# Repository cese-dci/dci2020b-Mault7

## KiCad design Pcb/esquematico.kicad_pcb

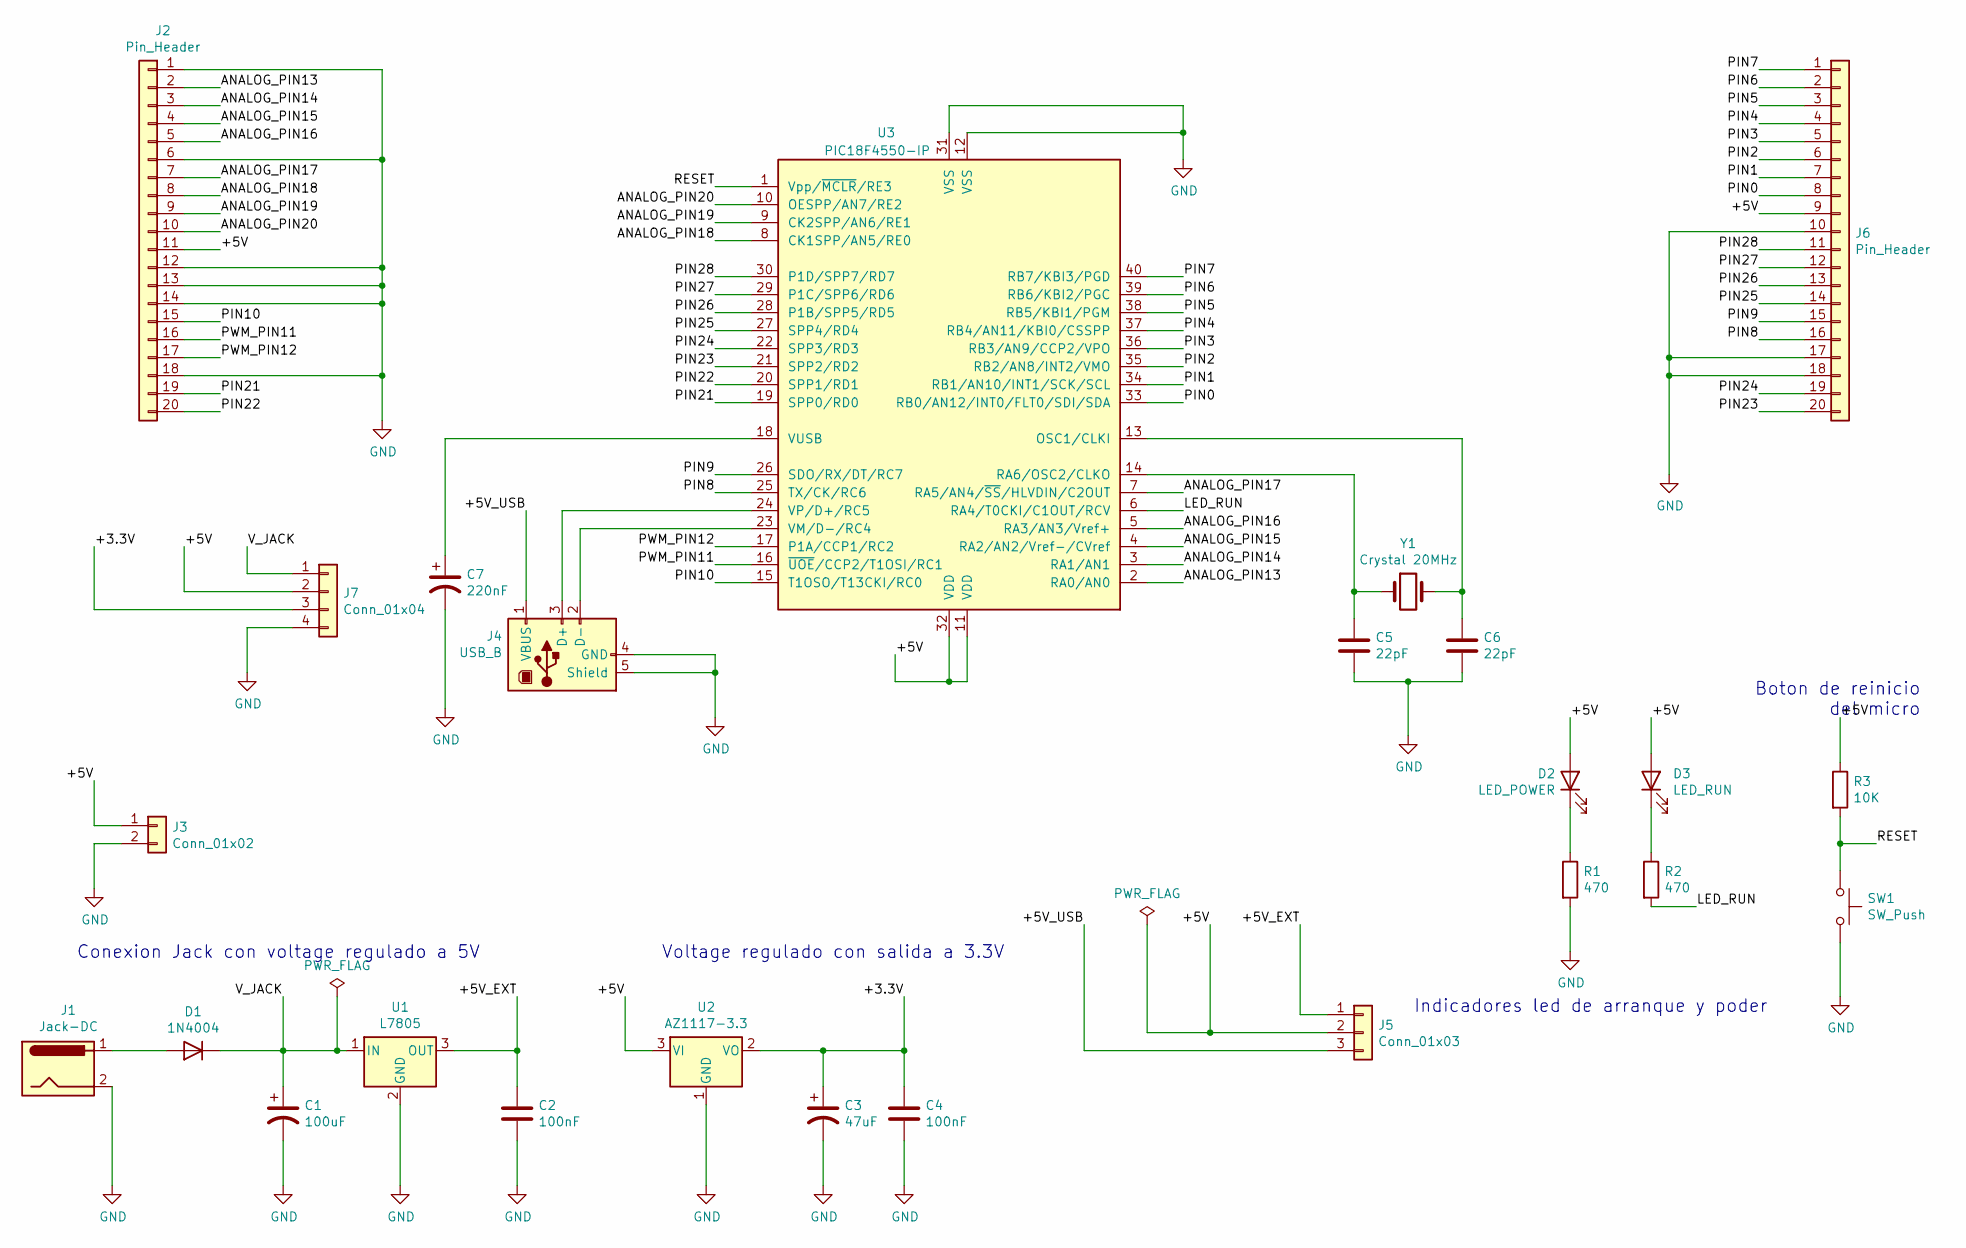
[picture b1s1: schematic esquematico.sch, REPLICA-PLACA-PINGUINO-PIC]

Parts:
C1: 100uF; CP_Radial_D5.0mm_P2.50mm
C2, C4: 100nF; C_Disc_D5.0mm_W2.5mm_P2.50mm
C3: 47uF; CP_Radial_D5.0mm_P2.50mm
C5, C6: 22pF; C_Disc_D3.8mm_W2.6mm_P2.50mm
C7: 220nF; CP_Radial_Tantal_D5.0mm_P5.00mm
D1: 1N4004; D_DO-41_SOD81_P7.62mm_Horizontal
D2: LED_POWER; LED_D3.0mm
D3: LED_RUN; LED_D3.0mm
J1: Jack-DC; BarrelJack_Horizontal
J2, J6: Pin_Header; PinSocket_1x20_P2.54mm_Vertical
J3: Conn_01x02; PinSocket_1x02_P2.54mm_Vertical
J4: USB_B; USB_B_Lumberg_2411_02_Horizontal
J5: Conn_01x03; PinHeader_1x03_P2.54mm_Vertical
J7: Conn_01x04; PinSocket_1x04_P2.54mm_Vertical
R1, R2: 470; R_Axial_DIN0207_L6.3mm_D2.5mm_P7.62mm_Horizontal
R3: 10K; R_Axial_DIN0207_L6.3mm_D2.5mm_P7.62mm_Horizontal
SW1: SW_Push; SW_PUSH_6mm_H7.3mm
U1: L7805; TO-3P-3_Vertical
U2: AZ1117-3.3; TO-3P-3_Vertical
U3: PIC18F4550-IP; DIP-40_W15.24mm
Y1: Crystal 20MHz; Crystal_HC18-U_Vertical

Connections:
/+3.3V: C3.1, C4.1, J7.3, U2.2 (VO)
/+5V: D2.2 (A), D3.2 (A), J2.11, J3.1, J5.2, J6.9, J7.2, R3.1, U2.3 (VI), U3.11 (VDD), U3.32 (VDD)
/+5V_EXT: C2.1, J5.1, U1.3 (OUT)
/+5V_USB: J4.1 (VBUS), J5.3
/ANALOG_PIN13: J2.2, U3.2 (RA0/AN0)
/ANALOG_PIN14: J2.3, U3.3 (RA1/AN1)
/ANALOG_PIN15: J2.4, U3.4 (RA2/AN2/Vref-/CVref)
/ANALOG_PIN16: J2.5, U3.5 (RA3/AN3/Vref+)
/ANALOG_PIN17: J2.7, U3.7 (RA5/AN4/~SS~/HLVDIN/C2OUT)
/ANALOG_PIN18: J2.8, U3.8 (CK1SPP/AN5/RE0)
/ANALOG_PIN19: J2.9, U3.9 (CK2SPP/AN6/RE1)
/ANALOG_PIN20: J2.10, U3.10 (OESPP/AN7/RE2)
/LED_RUN: R2.2, U3.6 (RA4/T0CKI/C1OUT/RCV)
/PIN0: J6.8, U3.33 (RB0/AN12/INT0/FLT0/SDI/SDA)
/PIN1: J6.7, U3.34 (RB1/AN10/INT1/SCK/SCL)
/PIN2: J6.6, U3.35 (RB2/AN8/INT2/VMO)
/PIN3: J6.5, U3.36 (RB3/AN9/CCP2/VPO)
/PIN4: J6.4, U3.37 (RB4/AN11/KBI0/CSSPP)
/PIN5: J6.3, U3.38 (RB5/KBI1/PGM)
/PIN6: J6.2, U3.39 (RB6/KBI2/PGC)
/PIN7: J6.1, U3.40 (RB7/KBI3/PGD)
/PIN8: J6.16, U3.25 (TX/CK/RC6)
/PIN9: J6.15, U3.26 (SDO/RX/DT/RC7)
/PIN10: J2.15, U3.15 (T1OSO/T13CKI/RC0)
/PIN21: J2.19, U3.19 (SPP0/RD0)
/PIN22: J2.20, U3.20 (SPP1/RD1)
/PIN23: J6.20, U3.21 (SPP2/RD2)
/PIN24: J6.19, U3.22 (SPP3/RD3)
/PIN25: J6.14, U3.27 (SPP4/RD4)
/PIN26: J6.13, U3.28 (P1B/SPP5/RD5)
/PIN27: J6.12, U3.29 (P1C/SPP6/RD6)
/PIN28: J6.11, U3.30 (P1D/SPP7/RD7)
/PWM_PIN11: J2.16, U3.16 (~UOE~/CCP2/T1OSI/RC1)
/PWM_PIN12: J2.17, U3.17 (P1A/CCP1/RC2)
/RESET: R3.2, SW1.1, U3.1 (Vpp/~MCLR~/RE3)
/V_JACK: C1.1, D1.1 (K), J7.1, U1.1 (IN)
GND: C1.2, C2.2, C3.2, C4.2, C5.2, C6.2, C7.2, J1.2, J2.1, J2.6, J2.12, J2.13, J2.14, J2.18, J3.2, J4.4 (GND), J4.5 (Shield), J6.10, J6.17, J6.18, J7.4, R1.2, SW1.2, U1.2 (GND), U2.1 (GND), U3.12 (VSS), U3.31 (VSS)
unnamed: C5.1, U3.14 (RA6/OSC2/CLKO), Y1.1
unnamed: C6.1, U3.13 (OSC1/CLKI), Y1.2
unnamed: C7.1, U3.18 (VUSB)
unnamed: D1.2 (A), J1.1
unnamed: D2.1 (K), R1.1
unnamed: D3.1 (K), R2.1
unnamed: J4.2 (D-), U3.23 (VM/D-/RC4)
unnamed: J4.3 (D+), U3.24 (VP/D+/RC5)

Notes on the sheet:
Conexion Jack con voltage regulado a 5V
Voltage regulado con salida a 3.3V
Boton de reinicio del micro
Indicadores led de arranque y poder

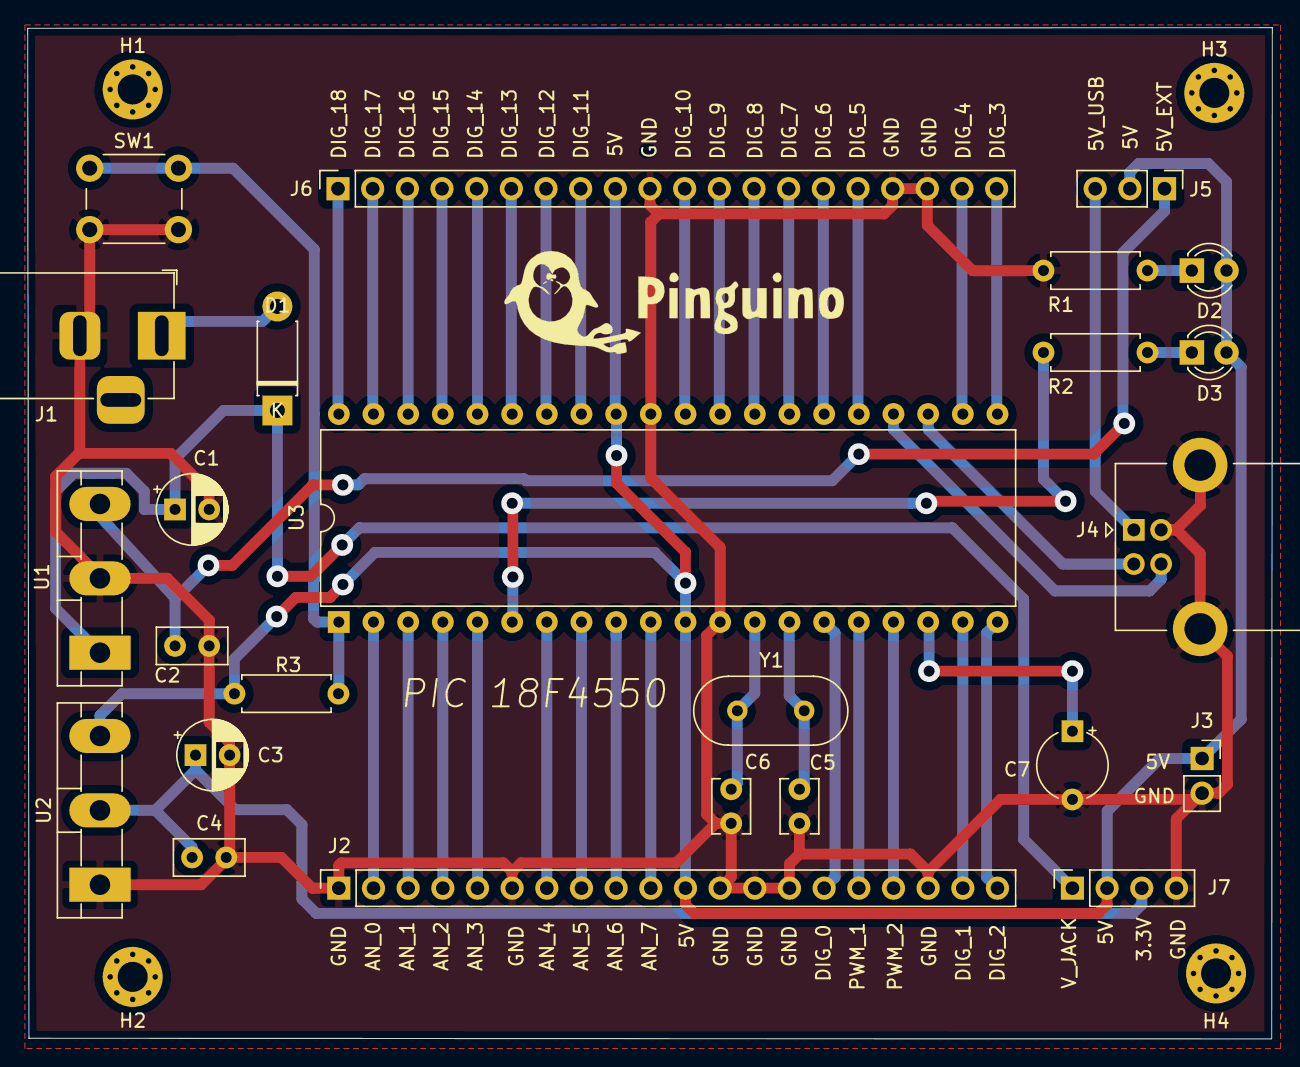
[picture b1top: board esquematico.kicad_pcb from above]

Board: 2 copper layers, 91.2 x 74.1 mm, 29 parts (0 on the bottom side), 45 nets.

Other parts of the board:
H1, H2, H3, H4: MountingHole; MountingHole_2.2mm_M2_Pad_Via

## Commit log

2020-10-09 commit init
2020-10-14 correcciones de errores de conexion
2020-11-02 se agrego datos faltantes al rotulo
2020-11-09 ultimas correcciones
2020-11-09 se agrego comentarios del diseno

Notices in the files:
Pcb/esquematico.kicad_pcb:
Licencia BSD (proyecto CIAA), GPL o OHL (Cern
